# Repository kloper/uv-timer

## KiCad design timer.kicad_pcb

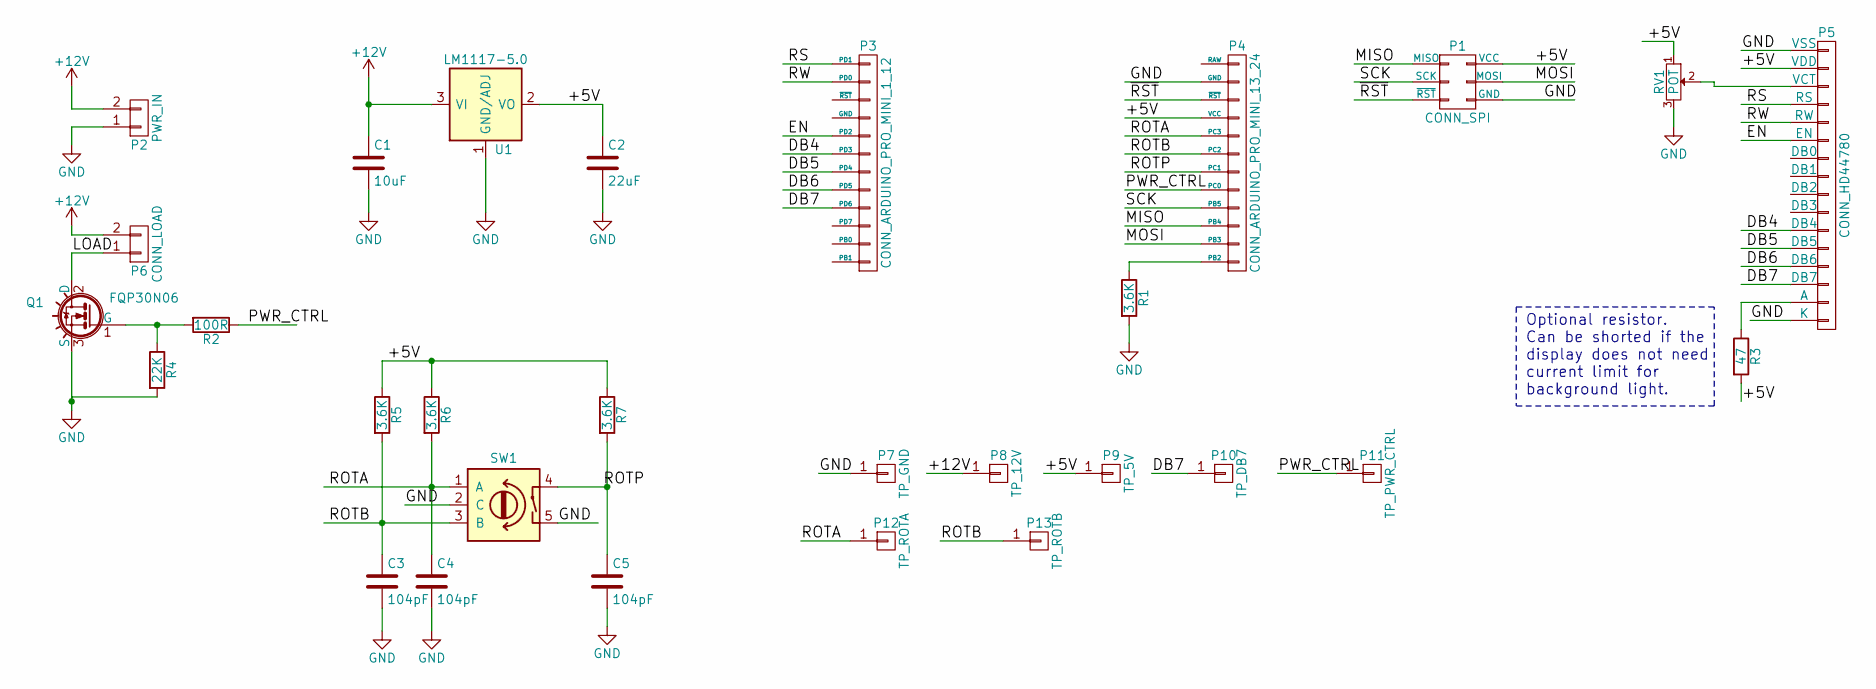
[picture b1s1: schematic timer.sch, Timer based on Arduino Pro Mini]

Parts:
C1: 10uF; C_Disc_D3_P2.5
C2: 22uF; C_Disc_D3_P2.5
C3, C4, C5: 104pF; C_Disc_D3_P2.5
P1: CONN_SPI; Pin_Header_Straight_2x03
P2: PWR_IN; Socket_Strip_Straight_1x02
P3: CONN_ARDUINO_PRO_MINI_1_12
P4: CONN_ARDUINO_PRO_MINI_13_24; Socket_Strip_Straight_1x12
P5: CONN_HD44780; Socket_Strip_Straight_1x16
P6: CONN_LOAD; Pin_Header_Straight_1x02
P7: TP_GND; Pin_Header_Straight_1x01
P8: TP_12V; Pin_Header_Straight_1x01
P9: TP_5V; Pin_Header_Straight_1x01
P10: TP_DB7; Pin_Header_Straight_1x01
P11: TP_PWR_CTRL; Pin_Header_Straight_1x01
P12: TP_ROTA; Pin_Header_Straight_1x01
P13: TP_ROTB; Pin_Header_Straight_1x01
Q1: FQP30N06; TO-220
R1, R5, R6, R7: 3.6K; Resistor_Horizontal_RM12mm
R2: 100R; Resistor_Horizontal_RM12mm
R3: 47; Resistor_Horizontal_RM12mm
R4: 22K; Resistor_Horizontal_RM12mm
RV1: POT; Potentiometer_Trimmer-Suntan-TSR-3386C
SW1: ROTARY_ENCODER_SWITCH; Pin_Header_Straight_2x03
U1: LM1117-5.0; SOT-223

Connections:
+12V: C1.1, P2.2, P6.2, P8.1, U1.3 (VI)
/+5V: C2.1, P1.2 (VCC), P4.4 (VCC), P5.2 (VDD), P9.1, R3.2, R5.1, R6.1, R7.1, RV1.1, U1.2 (VO), U1.4 (VO)
/DB4: P3.6 (PD3), P5.11 (DB4)
/DB5: P3.7 (PD4), P5.12 (DB5)
/DB6: P3.8 (PD5), P5.13 (DB6)
/DB7: P3.9 (PD6), P5.14 (DB7), P10.1
/EN: P3.5 (PD2), P5.6 (EN)
/LOAD: P6.1, Q1.2 (D)
/MISO: P1.1 (MISO), P4.10 (PB4)
/MOSI: P1.4 (MOSI), P4.11 (PB3)
/PWR_CTRL: P4.8 (PC0), P11.1, R2.1
/ROTA: C4.1, P4.5 (PC3), P12.1, R6.2, SW1.1 (A)
/ROTB: C3.1, P4.6 (PC2), P13.1, R5.2, SW1.3 (B)
/ROTP: C5.1, P4.7 (PC1), R7.2, SW1.4
/RS: P3.1 (PD1), P5.4 (RS)
/RW: P3.2 (PD0), P5.5 (RW)
/SCK: P1.3 (SCK), P4.9 (PB5)
/~RST: P1.5 (~RST), P4.3 (~RST)
GND: C1.2, C2.2, C3.2, C4.2, C5.2, P1.6 (GND), P2.1, P4.2 (GND), P5.1 (VSS), P5.16 (K), P7.1, Q1.3 (S), R1.2, R4.2, RV1.3, SW1.2 (C), SW1.5, U1.1 (GND/ADJ)
unnamed: P4.12 (PB2), R1.1
unnamed: P5.3 (VCT), RV1.2
unnamed: P5.15 (A), R3.1
unnamed: Q1.1 (G), R2.2, R4.1

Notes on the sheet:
Optional resistor. Can be shorted if the display does not need current limit for background light.

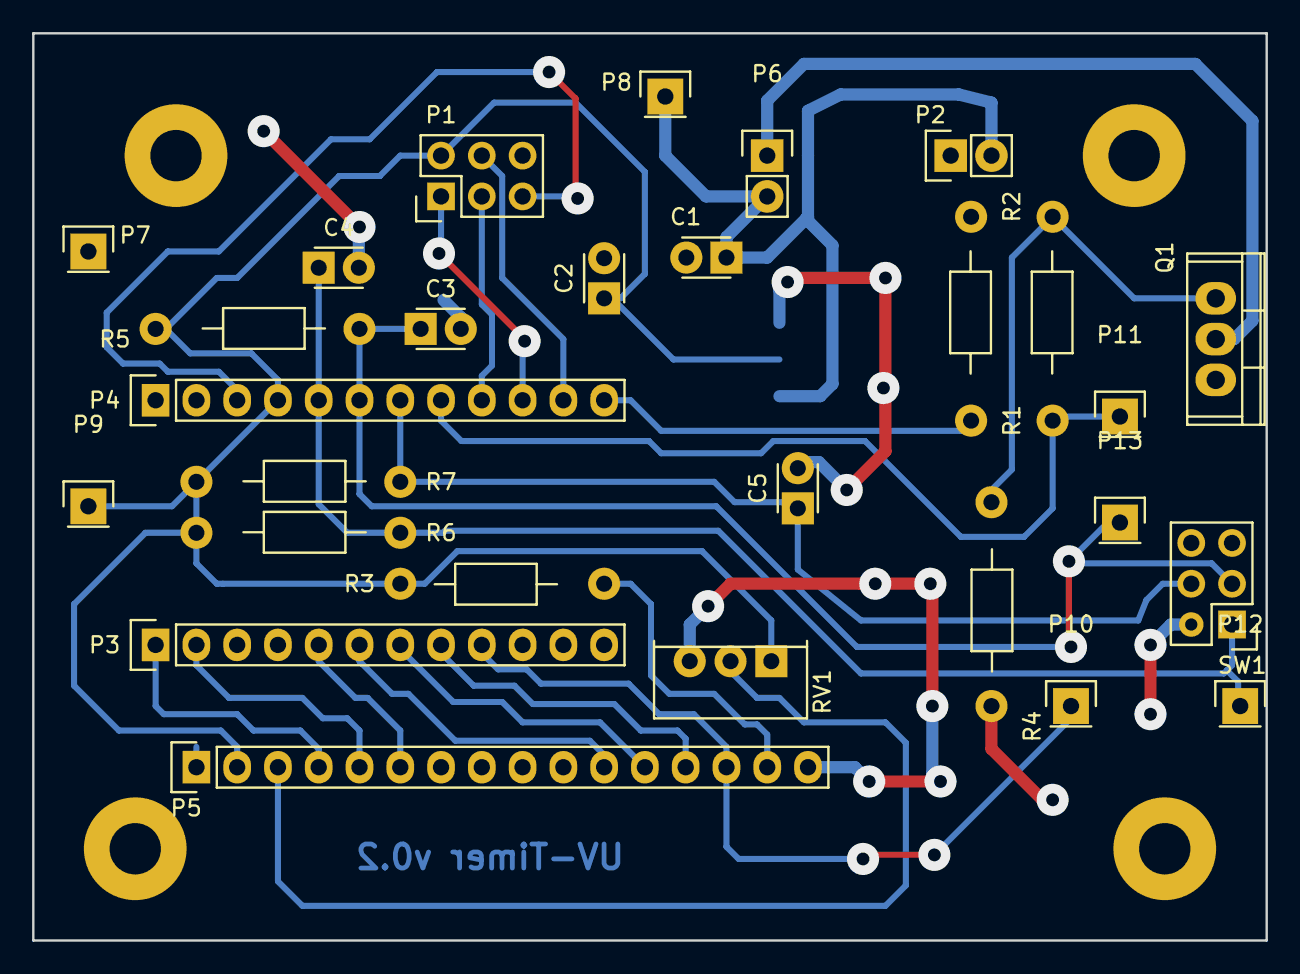
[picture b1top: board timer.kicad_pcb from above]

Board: 2 copper layers, 76.8 x 56.5 mm, 29 parts (1 on the bottom side), 23 nets.

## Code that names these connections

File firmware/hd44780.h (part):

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#if defined(__AVR_ATmega328P__) || defined(__AVR_ATmega328__)
#define HD44780_CTRL_PORT PORTD

#define HD44780_RS PD1
#define HD44780_RW PD0
#define HD44780_EN PD2
#define HD44780_RST PD7

#define HD44780_DATA_PORT PORTD

#define HD44780_DB4 PD3
#define HD44780_DB5 PD4
#define HD44780_DB6 PD5
#define HD44780_DB7 PD6
#endif

#define HD44780_BUSY HD44780_DB7
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
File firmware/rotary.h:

/** -*- C -*-
 * @file
 *
 * @brief Rotary encoder driver
 *
 * Copyright (c) 2014-2017 Dimitry Kloper <kloper@users.sf.net>. 
 * All rights reserved.
 *
 * @page License
 *
 * Redistribution and use in source and binary forms, with or without
 * modification, are permitted provided that the following conditions are
 * met:
 * 
 * 1. Redistributions of source code must retain the above copyright
 *    notice, this list of conditions and the following disclaimer.
 * 
 * 2. Redistributions in binary form must reproduce the above copyright
 *    notice, this list of conditions and the following disclaimer in the
 *    documentation and/or other materials provided with the
 *    distribution.
 * 
 * THIS SOFTWARE IS PROVIDED BY THE COPYRIGHT HOLDERS AND CONTRIBUTORS
 * "AS IS" AND ANY EXPRESS OR IMPLIED WARRANTIES, INCLUDING, BUT NOT
 * LIMITED TO, THE IMPLIED WARRANTIES OF MERCHANTABILITY AND FITNESS FOR
 * A PARTICULAR PURPOSE ARE DISCLAIMED. IN NO EVENT SHALL THE COPYRIGHT
 * OWNER OR CONTRIBUTORS BE LIABLE FOR ANY DIRECT, INDIRECT, INCIDENTAL,
 * SPECIAL, EXEMPLARY, OR CONSEQUENTIAL DAMAGES (INCLUDING, BUT NOT
 * LIMITED TO, PROCUREMENT OF SUBSTITUTE GOODS OR SERVICES; LOSS OF USE,
 * DATA, OR PROFITS; OR BUSINESS INTERRUPTION) HOWEVER CAUSED AND ON ANY
 * THEORY OF LIABILITY, WHETHER IN CONTRACT, STRICT LIABILITY, OR TORT
 * (INCLUDING NEGLIGENCE OR OTHERWISE) ARISING IN ANY WAY OUT OF THE USE
 * OF THIS SOFTWARE, EVEN IF ADVISED OF THE POSSIBILITY OF SUCH DAMAGE.
 * 
 * The views and conclusions contained in the software and documentation
 * are those of the authors and should not be interpreted as representing
 * official policies, either expressed or implied, of the Pato Project.
 */

#ifndef _uv_timer_rotary_h_
#define _uv_timer_rotary_h_

#define ROTA PC3
#define ROTB PC2
#define ROTP PC1

extern void rotary_init(void);
extern uint32_t rotary_get_rotary_counter(void);
extern uint32_t rotary_get_press_counter(void);

#endif /* _uv_timer_rotary_h_ */

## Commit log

2016-09-09 Initial import of UV Timer KiCad project and initial firmware.
2016-09-10 Introduced rotary switch driver
    The driver is based on edge detection interrupt and a timer for
    delayed input sampling to get rid of ringing.
2016-09-11 Fixed F_CPU frequency value to the real one
2016-09-11 Removed debug GPIO banging in rotary
2016-09-11 Introduced the basic real time timer and minimal terminal UI layer
2016-09-12 Compile with printf_min library
    Required for later uv_counter_t formatting
2016-09-12 Fix wrong backward focus setting
    This is due to wrong interpretation of C modulo operator
    which seems to work more like reminder operator.
2016-09-12 Introduce uv_counter_t UI control
    This is for setting decimal time fields in
    predefined range.
2016-09-12 Implement mode change and part of starting/stopping
    The change_mode() function is populated and changes frame layout
    depending on current mode.
    Start and Stop buttons are now behave as expected.
2016-09-14 Fix frame resetting when stopping timer
2016-09-14 Created timer alarm and actual count down
2016-09-14 Removed bug notification from schematics...
    ...it is already fixed.
2016-09-15 Make timer save current alarm value in EEPROM
    The value is saved on start of countdown and retrieved at boot time.
    This is usability feature.
2016-09-15 Fix remaining_value calculation...
    ... that can go negative if the timer stopped manually.
2016-09-15 Unset alarm on stop of countdown
    This is required when stopping timer manually
2016-09-15 Make remaining value the current alarm value if stopped manually
2016-09-15 Minor fixes in kicad project
